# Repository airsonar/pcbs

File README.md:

<!--
SPDX-FileCopyrightText: AirSonar contributors
SPDX-License-Identifier: CERN-OHL-W-2.0
-->

# AirSonar PCBs

This repository contains designs for PCBs used with the AirSonar project.

## Licensing

The designs and documentation for the circuit boards in this repository are licensed
under the [CERN Open Hardware Licence Version 2 - Weakly Reciprocal][CERNOHL] license
(SPDX code [CERN-OHL-W-2.0][SPDX]). The weakly reciprocal version requires that if you
modify the designs, you release them under an open license. Incorporating the designs
into a larger project does not require that project to be openly licensed (though we
would obviously encourage you to!).

[CERNOHL]: https://gitlab.com/ohwr/project/cernohl/-/wikis/Documents/CERN-OHL-version-2
[SPDX]: https://spdx.org/licenses/CERN-OHL-W-2.0.html

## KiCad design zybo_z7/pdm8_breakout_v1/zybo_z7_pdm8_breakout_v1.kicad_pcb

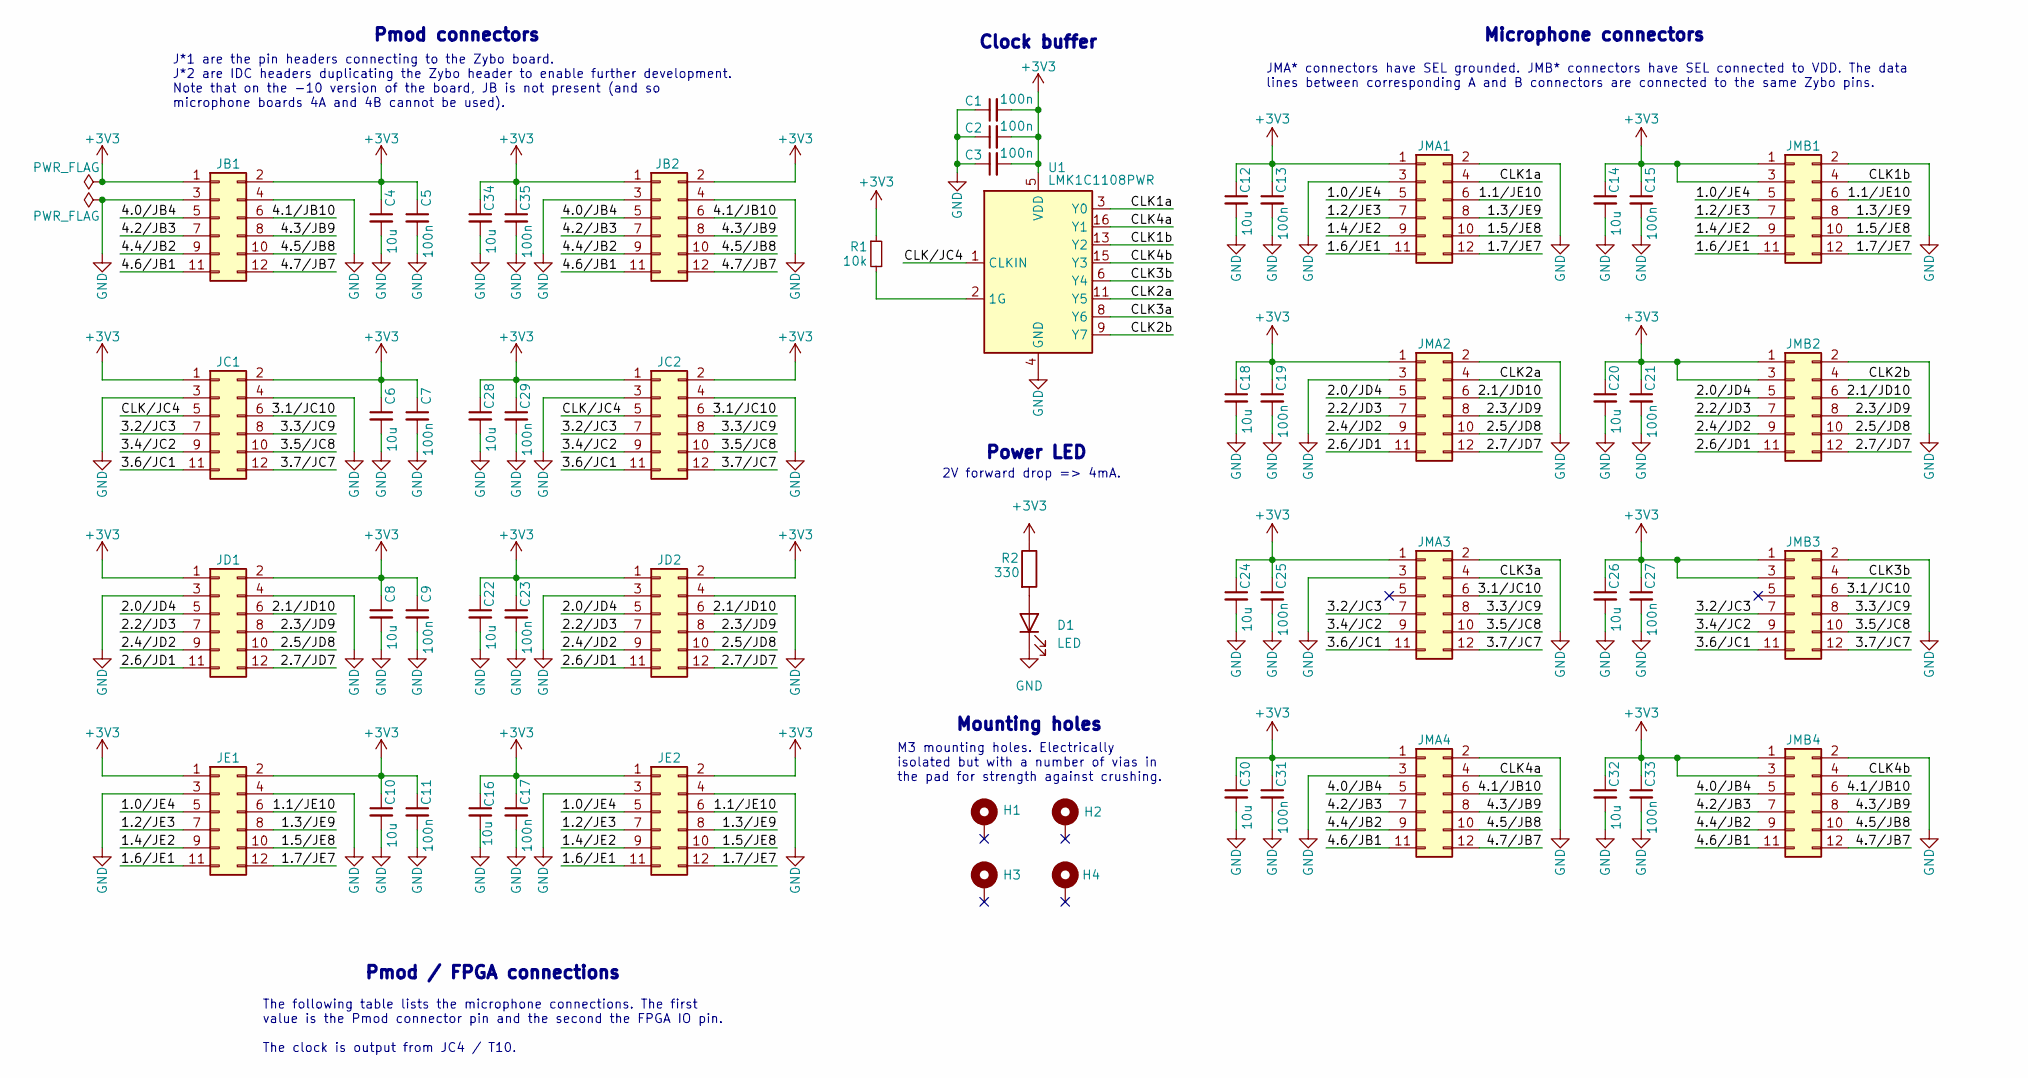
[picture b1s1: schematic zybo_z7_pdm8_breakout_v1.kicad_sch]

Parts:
C1, C2, C3, C5, C7, C9, C11, C13, C15, C17, C19, C21, C23, C25, C27, C29, C31, C33, C35: 100n; C_0603_1608Metric_Pad1.08x0.95mm_HandSolder
C4, C6, C8, C10, C12, C14, C16, C18, C20, C22, C24, C26, C28, C30, C32, C34: 10u; C_0603_1608Metric_Pad1.08x0.95mm_HandSolder
D1: LED; LED_0603_1608Metric
H1, H2, H3, H4: MountingHole_Pad; MountingHole_3.2mm_M3_Pad_Via
JB1: Conn_02x06_Odd_Even; PinHeader_2x06_P2.54mm_Horizontal
JB2: Conn_02x06_Odd_Even; IDC-Header_2x06_P2.54mm_Vertical_SMD
JC1: Conn_02x06_Odd_Even; PinHeader_2x06_P2.54mm_Horizontal
JC2: Conn_02x06_Odd_Even; IDC-Header_2x06_P2.54mm_Vertical_SMD
JD1: Conn_02x06_Odd_Even; PinHeader_2x06_P2.54mm_Horizontal
JD2: Conn_02x06_Odd_Even; IDC-Header_2x06_P2.54mm_Vertical_SMD
JE1: Conn_02x06_Odd_Even; PinHeader_2x06_P2.54mm_Horizontal
JE2: Conn_02x06_Odd_Even; IDC-Header_2x06_P2.54mm_Vertical_SMD
JMA1, JMA2, JMA3, JMA4: Conn_02x06_Odd_Even; IDC-Header_2x06_P2.54mm_Vertical_SMD
JMB1, JMB2, JMB3, JMB4: Conn_02x06_Odd_Even; IDC-Header_2x06_P2.54mm_Vertical_SMD
R1: 10k; R_0603_1608Metric_Pad0.98x0.95mm_HandSolder
R2: 330; R_0603_1608Metric_Pad0.98x0.95mm_HandSolder
U1: LMK1C1108PWR; TSSOP-16_4.4x5mm_P0.65mm

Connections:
+3V3: C1.2, C2.2, C3.2, C4.1, C5.1, C6.1, C7.1, C8.1, C9.1, C10.1, C11.1, C12.1, C13.1, C14.1, C15.1, C16.1, C17.1, C18.1, C19.1, C20.1, C21.1, C22.1, C23.1, C24.1, C25.1, C26.1, C27.1, C28.1, C29.1, C30.1, C31.1, C32.1, C33.1, C34.1, C35.1, JB1.1, JB1.2, JB2.1, JB2.2, JC1.1, JC1.2, JC2.1, JC2.2, JD1.1, JD1.2, JD2.1, JD2.2, JE1.1, JE1.2, JE2.1, JE2.2, JMA1.1, JMA2.1, JMA3.1, JMA4.1, JMB1.1, JMB1.3, JMB2.1, JMB2.3, JMB3.1, JMB3.3, JMB4.1, JMB4.3, R1.1, R2.1, U1.5 (VDD), U1.10 (VDD), U1.14 (VDD)
/1.0/JE4: JE1.5, JE2.5, JMA1.5, JMB1.5
/1.1/JE10: JE1.6, JE2.6, JMA1.6, JMB1.6
/1.2/JE3: JE1.7, JE2.7, JMA1.7, JMB1.7
/1.3/JE9: JE1.8, JE2.8, JMA1.8, JMB1.8
/1.4/JE2: JE1.9, JE2.9, JMA1.9, JMB1.9
/1.5/JE8: JE1.10, JE2.10, JMA1.10, JMB1.10
/1.6/JE1: JE1.11, JE2.11, JMA1.11, JMB1.11
/1.7/JE7: JE1.12, JE2.12, JMA1.12, JMB1.12
/2.0/JD4: JD1.5, JD2.5, JMA2.5, JMB2.5
/2.1/JD10: JD1.6, JD2.6, JMA2.6, JMB2.6
/2.2/JD3: JD1.7, JD2.7, JMA2.7, JMB2.7
/2.3/JD9: JD1.8, JD2.8, JMA2.8, JMB2.8
/2.4/JD2: JD1.9, JD2.9, JMA2.9, JMB2.9
/2.5/JD8: JD1.10, JD2.10, JMA2.10, JMB2.10
/2.6/JD1: JD1.11, JD2.11, JMA2.11, JMB2.11
/2.7/JD7: JD1.12, JD2.12, JMA2.12, JMB2.12
/3.1/JC10: JC1.6, JC2.6, JMA3.6, JMB3.6
/3.2/JC3: JC1.7, JC2.7, JMA3.7, JMB3.7
/3.3/JC9: JC1.8, JC2.8, JMA3.8, JMB3.8
/3.4/JC2: JC1.9, JC2.9, JMA3.9, JMB3.9
/3.5/JC8: JC1.10, JC2.10, JMA3.10, JMB3.10
/3.6/JC1: JC1.11, JC2.11, JMA3.11, JMB3.11
/3.7/JC7: JC1.12, JC2.12, JMA3.12, JMB3.12
/4.0/JB4: JB1.5, JB2.5, JMA4.5, JMB4.5
/4.1/JB10: JB1.6, JB2.6, JMA4.6, JMB4.6
/4.2/JB3: JB1.7, JB2.7, JMA4.7, JMB4.7
/4.3/JB9: JB1.8, JB2.8, JMA4.8, JMB4.8
/4.4/JB2: JB1.9, JB2.9, JMA4.9, JMB4.9
/4.5/JB8: JB1.10, JB2.10, JMA4.10, JMB4.10
/4.6/JB1: JB1.11, JB2.11, JMA4.11, JMB4.11
/4.7/JB7: JB1.12, JB2.12, JMA4.12, JMB4.12
/CLK1a: JMA1.4, U1.3 (Y0)
/CLK1b: JMB1.4, U1.13 (Y2)
/CLK2a: JMA2.4, U1.11 (Y5)
/CLK2b: JMB2.4, U1.9 (Y7)
/CLK3a: JMA3.4, U1.8 (Y6)
/CLK3b: JMB3.4, U1.6 (Y4)
/CLK4a: JMA4.4, U1.16 (Y1)
/CLK4b: JMB4.4, U1.15 (Y3)
/CLK/JC4: JC1.5, JC2.5, U1.1 (CLKIN)
GND: C1.1, C2.1, C3.1, C4.2, C5.2, C6.2, C7.2, C8.2, C9.2, C10.2, C11.2, C12.2, C13.2, C14.2, C15.2, C16.2, C17.2, C18.2, C19.2, C20.2, C21.2, C22.2, C23.2, C24.2, C25.2, C26.2, C27.2, C28.2, C29.2, C30.2, C31.2, C32.2, C33.2, C34.2, C35.2, D1.1 (K), JB1.3, JB1.4, JB2.3, JB2.4, JC1.3, JC1.4, JC2.3, JC2.4, JD1.3, JD1.4, JD2.3, JD2.4, JE1.3, JE1.4, JE2.3, JE2.4, JMA1.2, JMA1.3, JMA2.2, JMA2.3, JMA3.2, JMA3.3, JMA4.2, JMA4.3, JMB1.2, JMB2.2, JMB3.2, JMB4.2, U1.4 (GND), U1.7 (GND), U1.12 (GND)
unnamed: D1.2 (A), R2.2
unnamed: R1.2, U1.2 (1G)

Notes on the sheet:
Clock buffer
Microphone connectors
Mounting holes
Power LED
Pmod connectors
Pmod / FPGA connections
JMA* connectors have SEL grounded. JMB* connectors have SEL connected to VDD. The data lines between corresponding A and B connectors are connected to the same Zybo pins.
M3 mounting holes. Electrically isolated but with a number of vias in the pad for strength against crushing.
J*1 are the pin headers connecting to the Zybo board. J*2 are IDC headers duplicating the Zybo header to enable further development. Note that on the -10 version of the board, JB is not present (and so microphone boards 4A and 4B cannot be used).
2V forward drop => 4mA.
The following table lists the microphone connections. The first value is the Pmod connector pin and the second the FPGA IO pin. The clock is output from JC4 / T10.

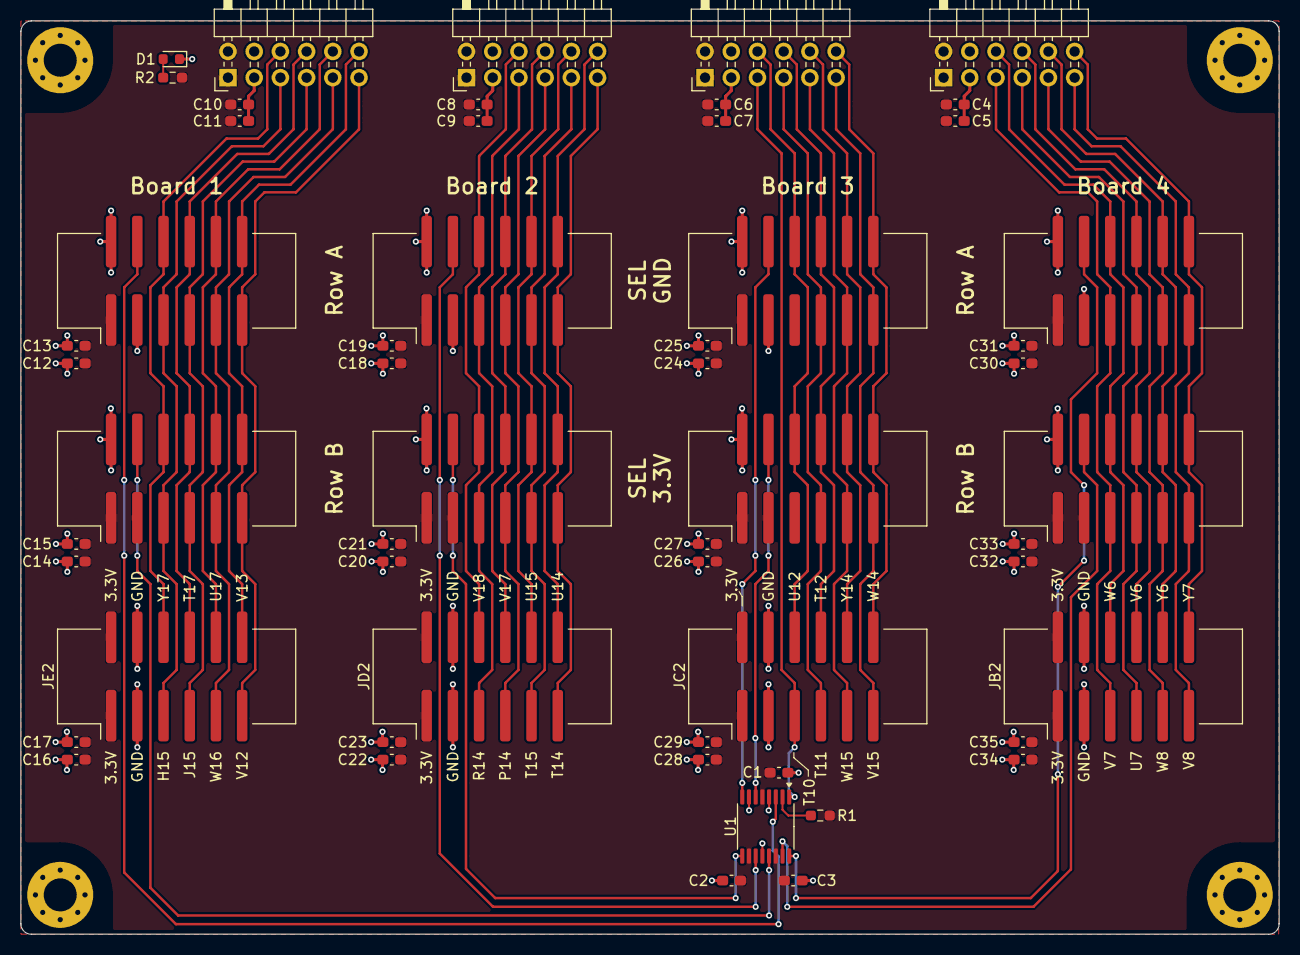
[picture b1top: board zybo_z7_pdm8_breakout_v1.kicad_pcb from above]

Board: 2 copper layers, 121.9 x 88.5 mm, 59 parts (0 on the bottom side), 44 nets.

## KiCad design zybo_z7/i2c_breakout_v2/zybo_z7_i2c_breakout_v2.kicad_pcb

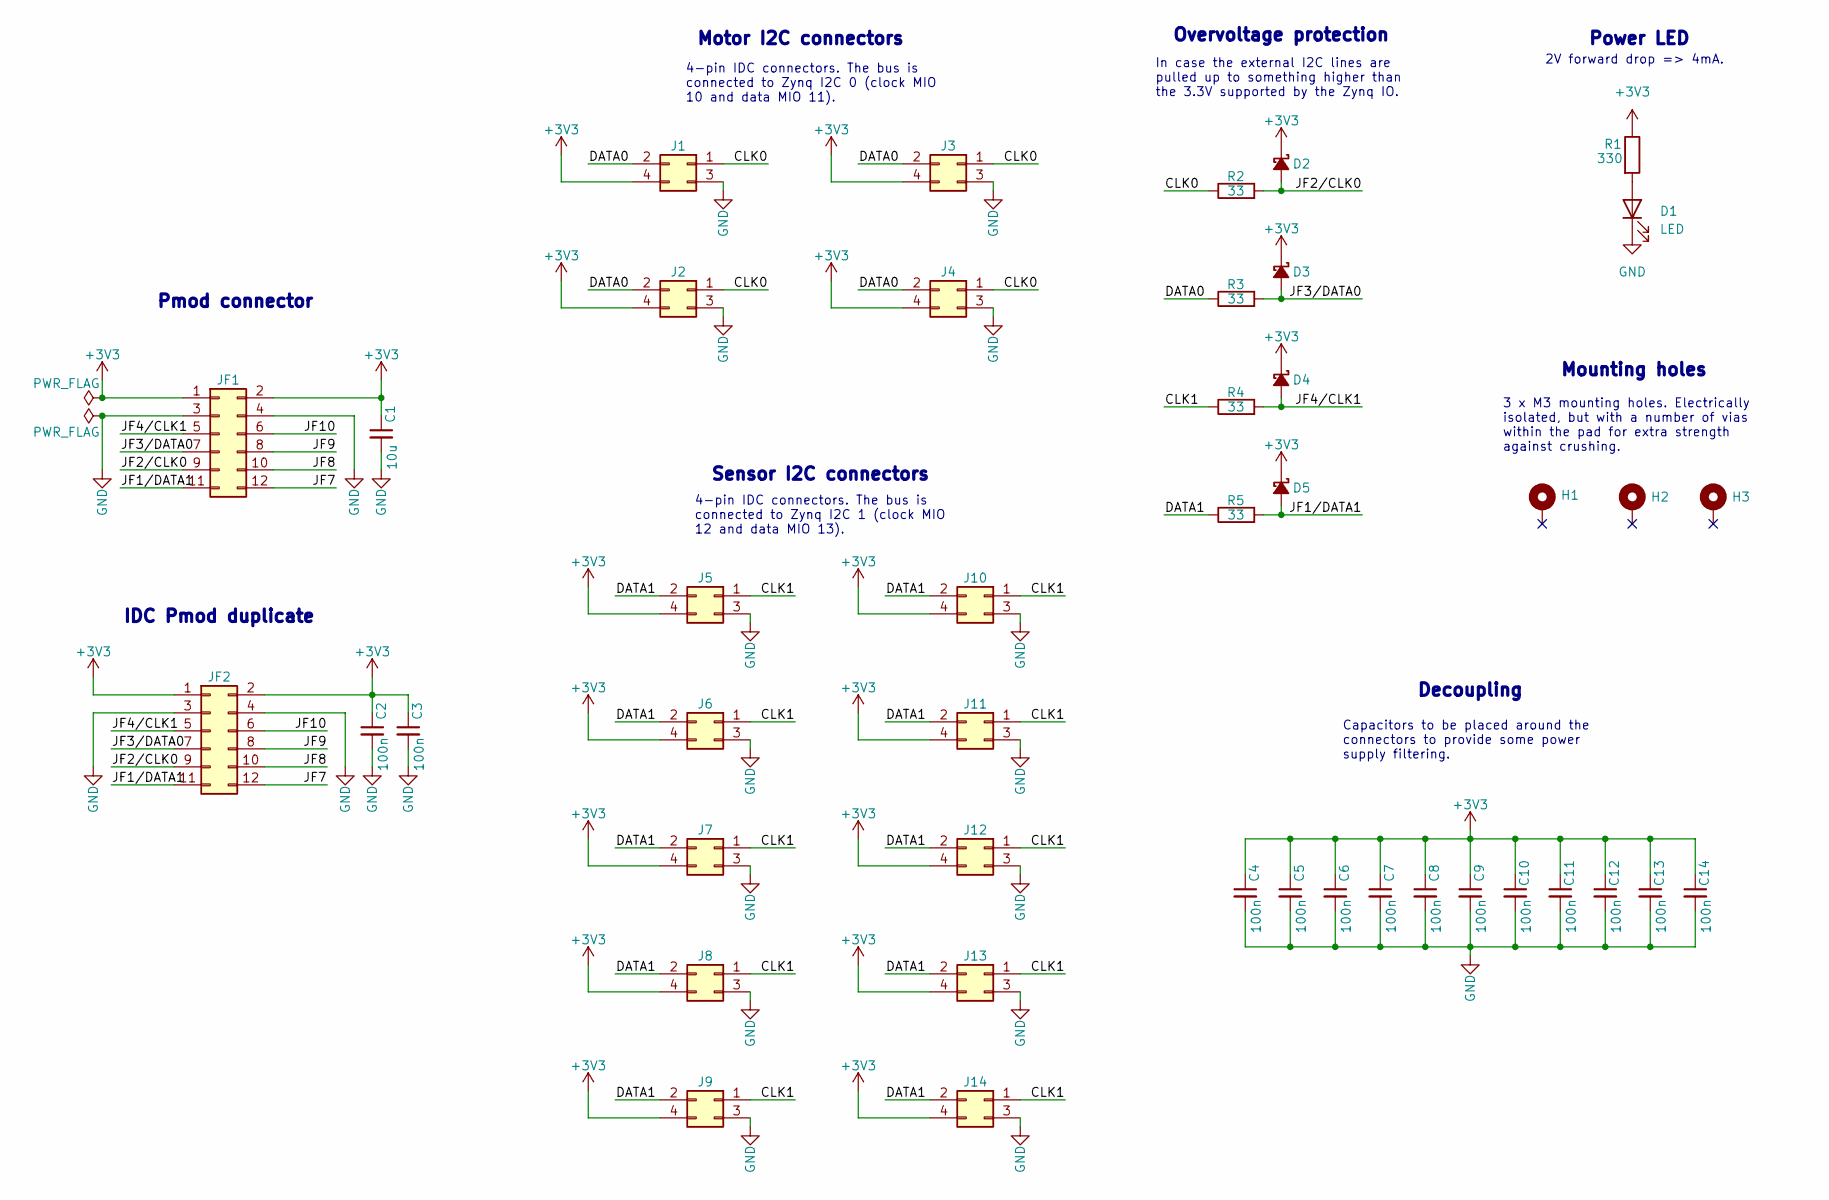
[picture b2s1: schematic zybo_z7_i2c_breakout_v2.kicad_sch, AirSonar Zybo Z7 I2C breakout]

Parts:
C1: 10u; C_0603_1608Metric_Pad1.08x0.95mm_HandSolder
C2, C3, C4, C5, C6, C7, C8, C9, C10, C11, C12, C13, C14: 100n; C_0603_1608Metric_Pad1.08x0.95mm_HandSolder
D1: LED; LED_0603_1608Metric
D2, D3, D4, D5: D_Schottky_Small_Filled; D_SOD-523
H1, H2, H3: MountingHole_Pad; MountingHole_3.2mm_M3_Pad_Via
J1, J2, J3, J4, J5, J6, J7, J8, J9, J10, J11, J12, J13, J14: Conn_02x02_Odd_Even; Amphenol_75869-130LF
JF1: Conn_02x06_Odd_Even; PinHeader_2x06_P2.54mm_Horizontal
JF2: Conn_02x06_Odd_Even; IDC-Header_2x06_P2.54mm_Vertical_SMD
R1: 330; R_0603_1608Metric_Pad0.98x0.95mm_HandSolder
R2, R3, R4, R5: 33; R_0603_1608Metric_Pad0.98x0.95mm_HandSolder

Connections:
+3V3: C1.1, C2.1, C3.1, C4.1, C5.1, C6.1, C7.1, C8.1, C9.1, C10.1, C11.1, C12.1, C13.1, C14.1, D2.1 (K), D3.1 (K), D4.1 (K), D5.1 (K), J1.4, J2.4, J3.4, J4.4, J5.4, J6.4, J7.4, J8.4, J9.4, J10.4, J11.4, J12.4, J13.4, J14.4, JF1.1, JF1.2, JF2.1, JF2.2, R1.1
/CLK0: J1.1, J2.1, J3.1, J4.1, R2.1
/CLK1: J5.1, J6.1, J7.1, J8.1, J9.1, J10.1, J11.1, J12.1, J13.1, J14.1, R4.1
/DATA0: J1.2, J2.2, J3.2, J4.2, R3.1
/DATA1: J5.2, J6.2, J7.2, J8.2, J9.2, J10.2, J11.2, J12.2, J13.2, J14.2, R5.1
/JF1/DATA1: D5.2 (A), JF1.11, JF2.11, R5.2
/JF2/CLK0: D2.2 (A), JF1.9, JF2.9, R2.2
/JF3/DATA0: D3.2 (A), JF1.7, JF2.7, R3.2
/JF4/CLK1: D4.2 (A), JF1.5, JF2.5, R4.2
/JF7: JF1.12, JF2.12
/JF8: JF1.10, JF2.10
/JF9: JF1.8, JF2.8
/JF10: JF1.6, JF2.6
GND: C1.2, C2.2, C3.2, C4.2, C5.2, C6.2, C7.2, C8.2, C9.2, C10.2, C11.2, C12.2, C13.2, C14.2, D1.1 (K), J1.3, J2.3, J3.3, J4.3, J5.3, J6.3, J7.3, J8.3, J9.3, J10.3, J11.3, J12.3, J13.3, J14.3, JF1.3, JF1.4, JF2.3, JF2.4
unnamed: D1.2 (A), R1.2

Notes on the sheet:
Sensor I2C connectors
Motor I2C connectors
Overvoltage protection
Pmod connector
Power LED
IDC Pmod duplicate
Mounting holes
Decoupling
4-pin IDC connectors. The bus is connected to Zynq I2C 0 (clock MIO 10 and data MIO 11).
4-pin IDC connectors. The bus is connected to Zynq I2C 1 (clock MIO 12 and data MIO 13).
Capacitors to be placed around the connectors to provide some power supply filtering.
2V forward drop => 4mA.
3 x M3 mounting holes. Electrically isolated, but with a number of vias within the pad for extra strength against crushing.
In case the external I2C lines are pulled up to something higher than the 3.3V supported by the Zynq IO.

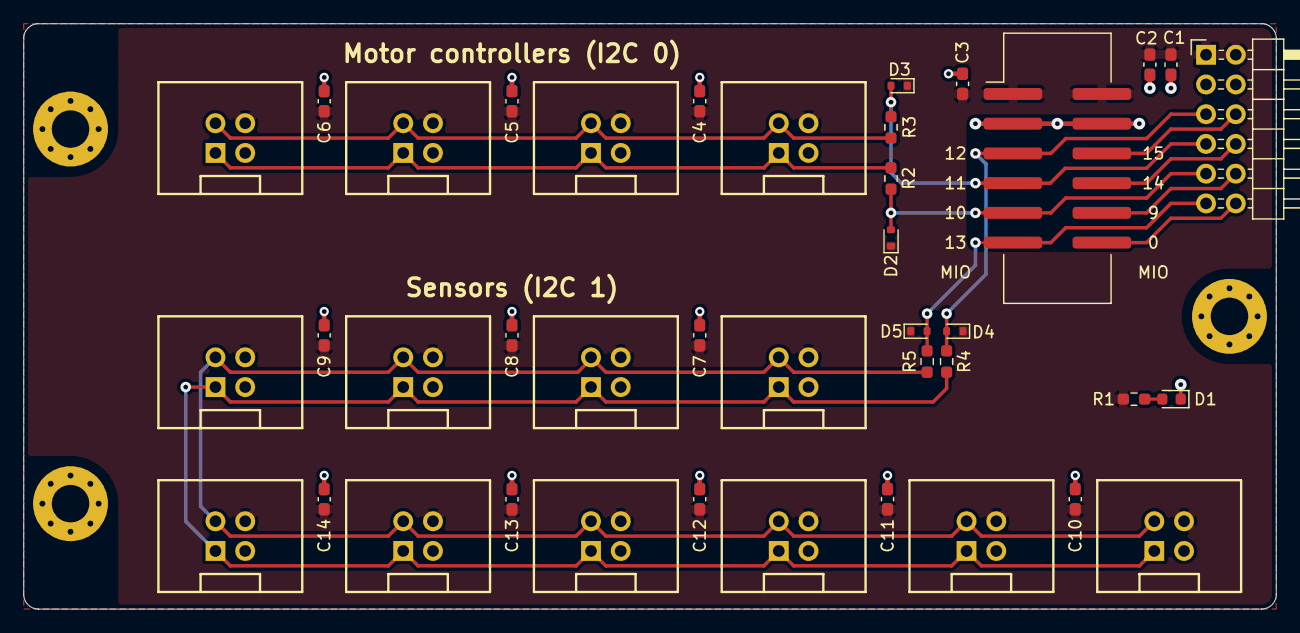
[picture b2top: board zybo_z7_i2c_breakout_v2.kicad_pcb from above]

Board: 2 copper layers, 107.0 x 50.0 mm, 43 parts (0 on the bottom side), 15 nets.

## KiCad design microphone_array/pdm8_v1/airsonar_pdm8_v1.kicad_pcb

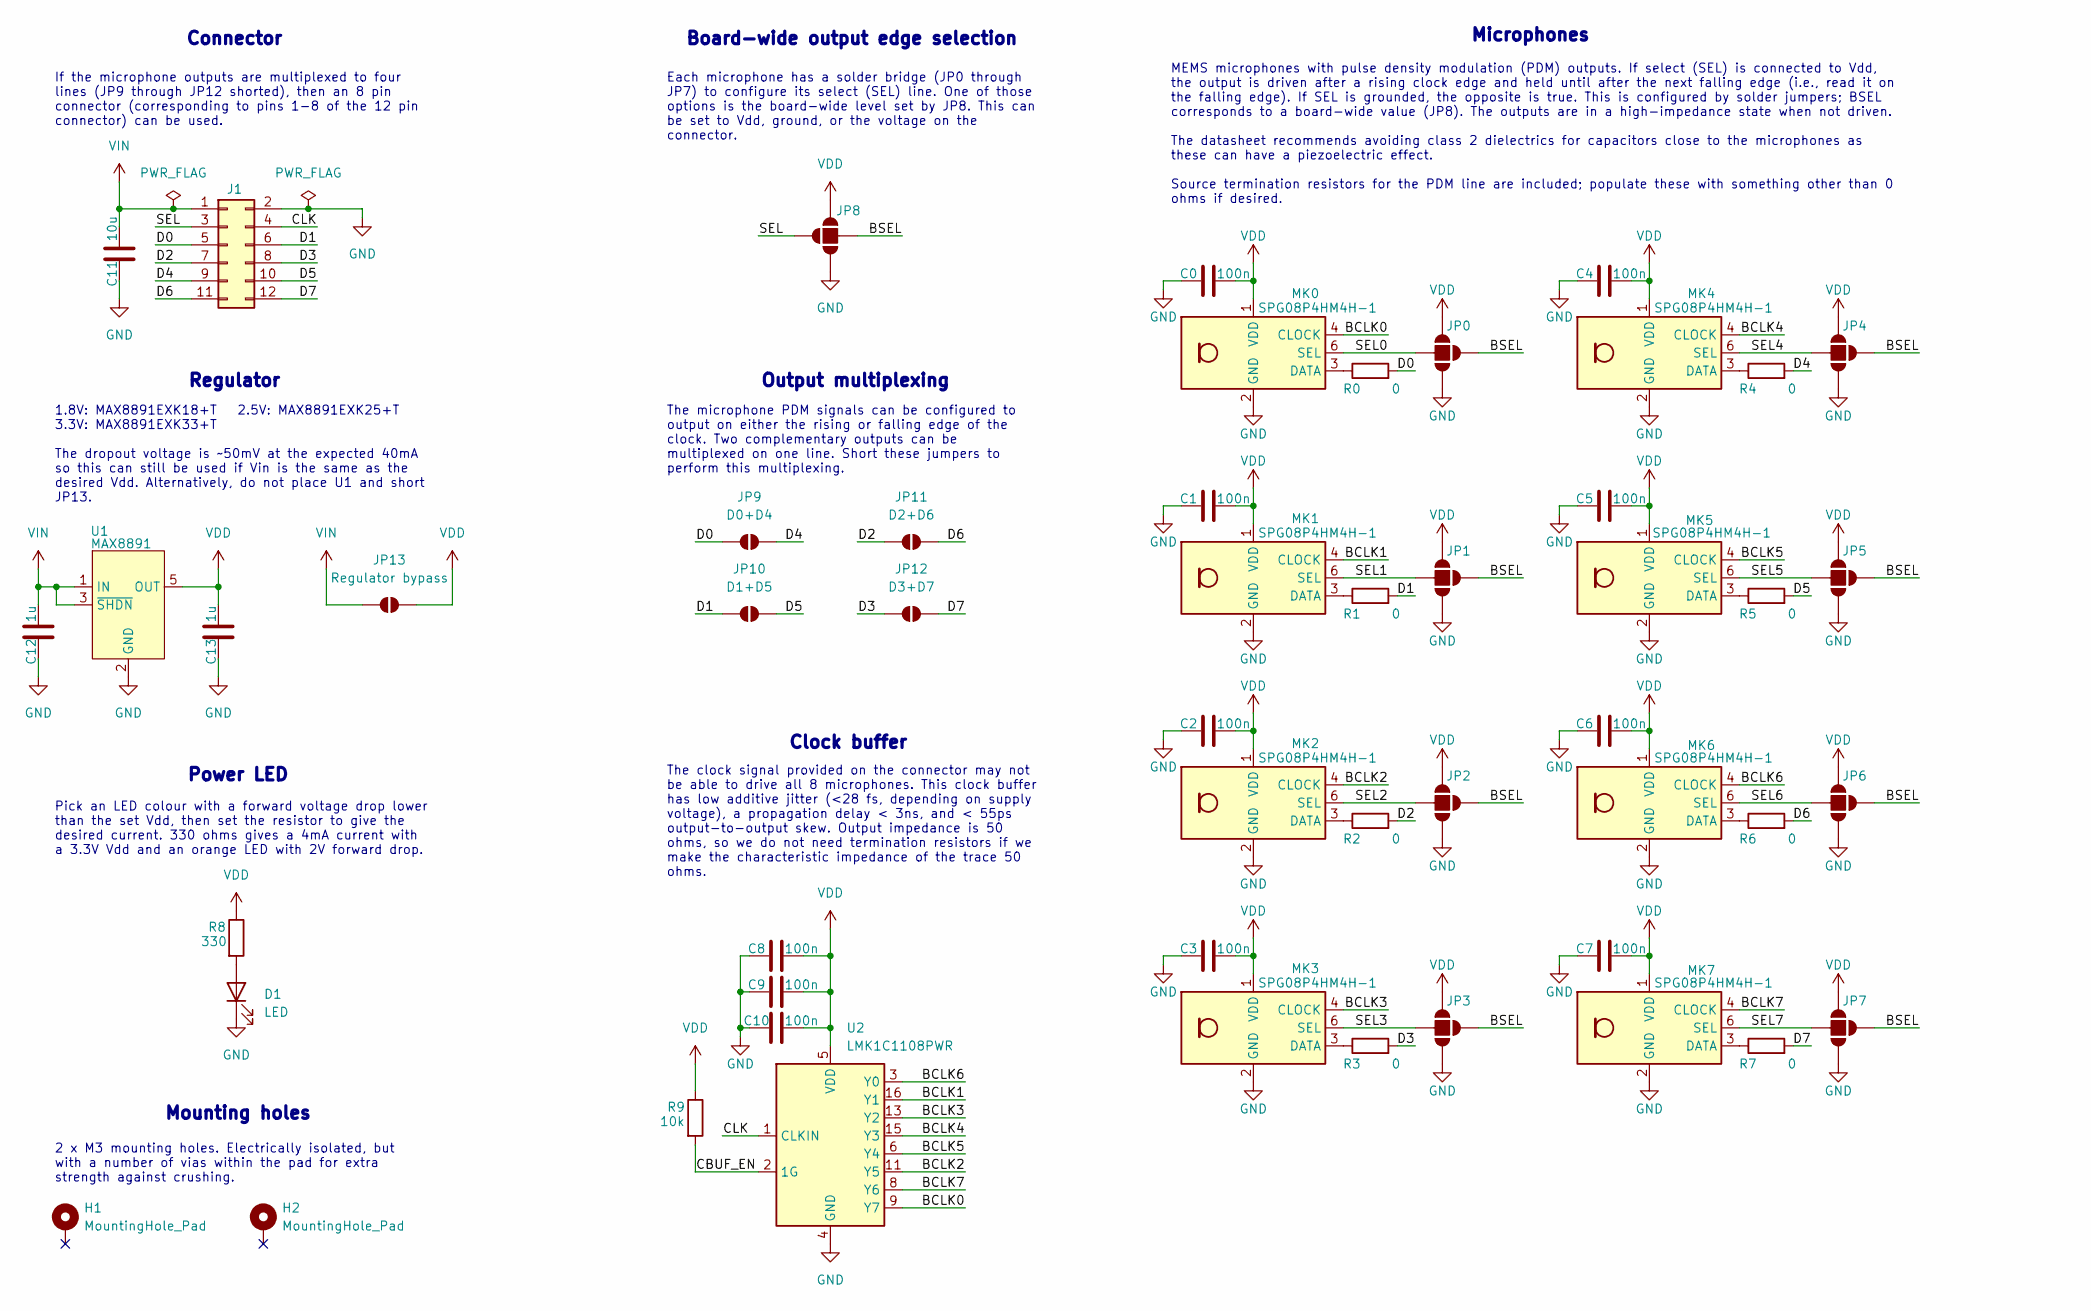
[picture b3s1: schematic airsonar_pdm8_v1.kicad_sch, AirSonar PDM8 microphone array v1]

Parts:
C0, C1, C2, C3, C4, C5, C6, C7, C8, C9, C10: 100n; C_0603_1608Metric_Pad1.08x0.95mm_HandSolder
C11: 10u; C_0603_1608Metric_Pad1.08x0.95mm_HandSolder
C12, C13: 1u; C_0603_1608Metric_Pad1.08x0.95mm_HandSolder
D1: LED; LED_0603_1608Metric
H1, H2: MountingHole_Pad; MountingHole_3.2mm_M3_Pad_Via
J1: Conn_02x06_Top_Bottom; IDC-Header_2x06_P2.54mm_Vertical_SMD
JP0: SEL0; SolderJumper-4-MicSelect
JP1: SEL1; SolderJumper-4-MicSelect
JP2: SEL2; SolderJumper-4-MicSelect
JP3: SEL3; SolderJumper-4-MicSelect
JP4: SEL4; SolderJumper-4-MicSelect
JP5: SEL5; SolderJumper-4-MicSelect
JP6: SEL6; SolderJumper-4-MicSelect
JP7: SEL7; SolderJumper-4-MicSelect
JP8: Board SEL; SolderJumper-4-BoardSelect
JP9: D0+D4; SolderJumper-2
JP10: D1+D5; SolderJumper-2
JP11: D2+D6; SolderJumper-2
JP12: D3+D7; SolderJumper-2
JP13: Regulator bypass; SolderJumper-2_P1.3mm_Open_RoundedPad1.0x1.5mm
MK0, MK1, MK2, MK3, MK4, MK5, MK6, MK7: SPG08P4HM4H-1; Knowles_SPG08P4HM4H-1_4x2mm
R0, R1, R2, R3, R4, R5, R6, R7: 0; R_0603_1608Metric_Pad0.98x0.95mm_HandSolder
R8: 330; R_0603_1608Metric_Pad0.98x0.95mm_HandSolder
R9: 10k; R_0603_1608Metric_Pad0.98x0.95mm_HandSolder
U1: MAX8891; SOT-353_SC-70-5_Handsoldering
U2: LMK1C1108PWR; TSSOP-16_4.4x5mm_P0.65mm

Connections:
/BCLK0: MK0.4 (CLOCK), U2.9 (Y7)
/BCLK1: MK1.4 (CLOCK), U2.16 (Y1)
/BCLK2: MK2.4 (CLOCK), U2.11 (Y5)
/BCLK3: MK3.4 (CLOCK), U2.13 (Y2)
/BCLK4: MK4.4 (CLOCK), U2.15 (Y3)
/BCLK5: MK5.4 (CLOCK), U2.6 (Y4)
/BCLK6: MK6.4 (CLOCK), U2.3 (Y0)
/BCLK7: MK7.4 (CLOCK), U2.8 (Y6)
/BSEL: JP0.3 (B), JP1.3 (B), JP2.3 (B), JP3.3 (B), JP4.3 (B), JP5.3 (B), JP6.3 (B), JP7.3 (B), JP8.1 (O)
/CBUF_EN: R9.2, U2.2 (1G)
/CLK: J1.4, U2.1 (CLKIN)
/D0: J1.5, JP9.1 (A), R0.2
/D1: J1.6, JP10.1 (A), R1.2
/D2: J1.7, JP11.1 (A), R2.2
/D3: J1.8, JP12.1 (A), R3.2
/D4: J1.9, JP9.2 (B), R4.2
/D5: J1.10, JP10.2 (B), R5.2
/D6: J1.11, JP11.2 (B), R6.2
/D7: J1.12, JP12.2 (B), R7.2
/SEL: J1.3, JP8.3 (B)
/SEL0: JP0.1 (O), MK0.6 (SEL)
/SEL1: JP1.1 (O), MK1.6 (SEL)
/SEL2: JP2.1 (O), MK2.6 (SEL)
/SEL3: JP3.1 (O), MK3.6 (SEL)
/SEL4: JP4.1 (O), MK4.6 (SEL)
/SEL5: JP5.1 (O), MK5.6 (SEL)
/SEL6: JP6.1 (O), MK6.6 (SEL)
/SEL7: JP7.1 (O), MK7.6 (SEL)
GND: C0.1, C1.1, C2.1, C3.1, C4.1, C5.1, C6.1, C7.1, C8.1, C9.1, C10.1, C11.1, C12.1, C13.1, D1.1 (K), J1.2, JP0.4 (C), JP1.4 (C), JP2.4 (C), JP3.4 (C), JP4.4 (C), JP5.4 (C), JP6.4 (C), JP7.4 (C), JP8.4 (C), MK0.2 (GND), MK0.5 (GND), MK1.2 (GND), MK1.5 (GND), MK2.2 (GND), MK2.5 (GND), MK3.2 (GND), MK3.5 (GND), MK4.2 (GND), MK4.5 (GND), MK5.2 (GND), MK5.5 (GND), MK6.2 (GND), MK6.5 (GND), MK7.2 (GND), MK7.5 (GND), U1.2 (GND), U2.4 (GND), U2.7 (GND), U2.12 (GND)
unnamed: D1.2 (A), R8.2
unnamed: MK0.3 (DATA), R0.1
unnamed: MK1.3 (DATA), R1.1
unnamed: MK2.3 (DATA), R2.1
unnamed: MK3.3 (DATA), R3.1
unnamed: MK4.3 (DATA), R4.1
unnamed: MK5.3 (DATA), R5.1
unnamed: MK6.3 (DATA), R6.1
unnamed: MK7.3 (DATA), R7.1
VDD: C0.2, C1.2, C2.2, C3.2, C4.2, C5.2, C6.2, C7.2, C8.2, C9.2, C10.2, C13.2, JP0.2 (A), JP1.2 (A), JP2.2 (A), JP3.2 (A), JP4.2 (A), JP5.2 (A), JP6.2 (A), JP7.2 (A), JP8.2 (A), JP13.2 (B), MK0.1 (VDD), MK1.1 (VDD), MK2.1 (VDD), MK3.1 (VDD), MK4.1 (VDD), MK5.1 (VDD), MK6.1 (VDD), MK7.1 (VDD), R8.1, R9.1, U1.5 (OUT), U2.5 (VDD), U2.10 (VDD), U2.14 (VDD)
VIN: C11.2, C12.2, J1.1, JP13.1 (A), U1.1 (IN), U1.3 (~SHDN)

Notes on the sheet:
Connector
Clock buffer
Output multiplexing
Power LED
Mounting holes
Microphones
Regulator
Board-wide output edge selection
The clock signal provided on the connector may not be able to drive all 8 microphones. This clock buffer has low additive jitter (<28 fs, depending on supply voltage), a propagation delay < 3ns, and < 55ps output-to-output skew. Output impedance is 50 ohms, so we do not need termination resistors i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
The microphone PDM signals can be configured to output on either the rising or falling edge of the clock. Two complementary outputs can be multiplexed on one line. Short these jumpers to perform this multiplexing.
Each microphone has a solder bridge (JP0 through JP7) to configure its select (SEL) line. One of those options is the board-wide level set by JP8. This can be set to Vdd, ground, or the voltage on the connector.
MEMS microphones with pulse density modulation (PDM) outputs. If select (SEL) is connected to Vdd, the output is driven after a rising clock edge and held until after the next falling edge (i.e., read it on the falling edge). If SEL is grounded, the opposite is true. This is configured by solder ju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
Pick an LED colour with a forward voltage drop lower than the set Vdd, then set the resistor to give the desired current. 330 ohms gives a 4mA current with a 3.3V Vdd and an orange LED with 2V forward drop.
2 x M3 mounting holes. Electrically isolated, but with a number of vias within the pad for extra strength against crushing.
1.8V: MAX8891EXK18+T 2.5V: MAX8891EXK25+T 3.3V: MAX8891EXK33+T The dropout voltage is ~50mV at the expected 40mA so this can still be used if Vin is the same as the desired Vdd. Alternatively, do not place U1 and short JP13.
If the microphone outputs are multiplexed to four lines (JP9 through JP12 shorted), then an 8 pin connector (corresponding to pins 1-8 of the 12 pin connector) can be used.

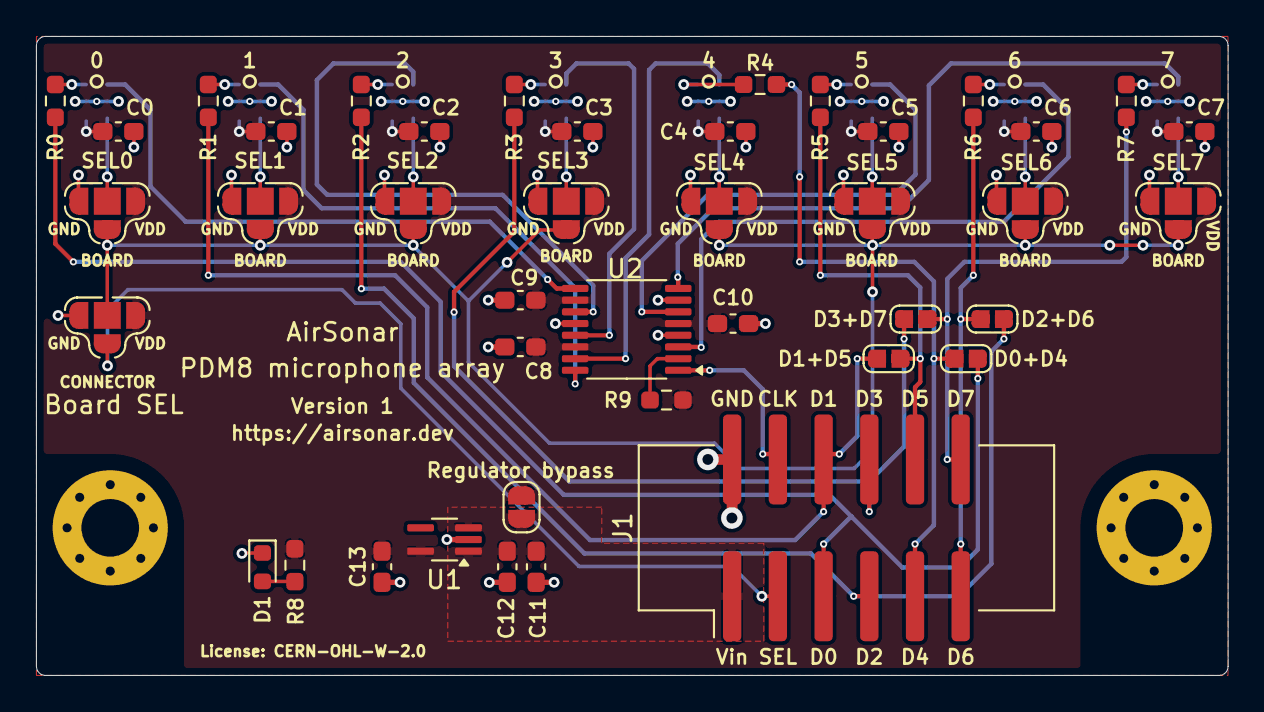
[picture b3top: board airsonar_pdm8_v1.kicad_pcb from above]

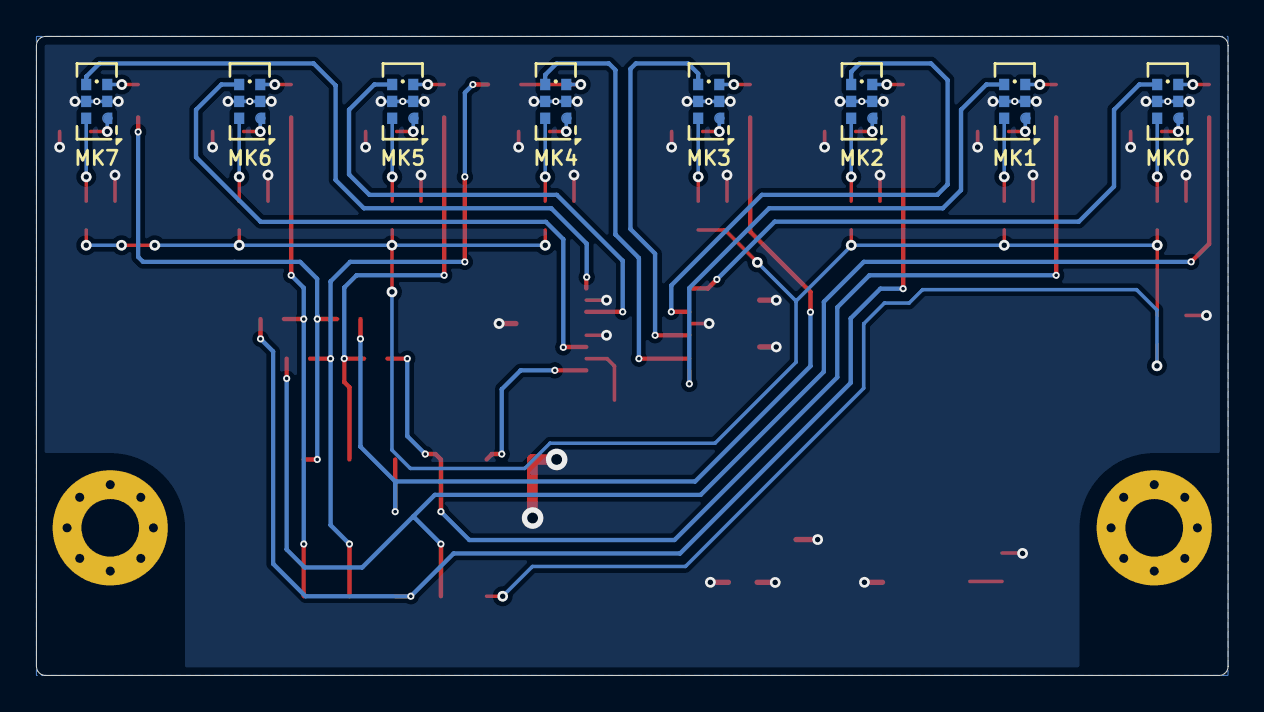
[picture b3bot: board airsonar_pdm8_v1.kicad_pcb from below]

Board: 4 copper layers, 66.2 x 35.5 mm, 52 parts (8 on the bottom side), 40 nets.

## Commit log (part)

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2026-04-17 Initialise repository and docs
2026-04-17 Import KiCad libraries and templates.
2026-04-18 Import v1 of PDM8 microphone array

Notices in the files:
microphone_array/pdm8_v1/airsonar_pdm8_v1.kicad_pcb:
License: CERN-OHL-W-2.0
